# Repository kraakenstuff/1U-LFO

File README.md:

# 1U-LFO
1U Eurorack LFO module

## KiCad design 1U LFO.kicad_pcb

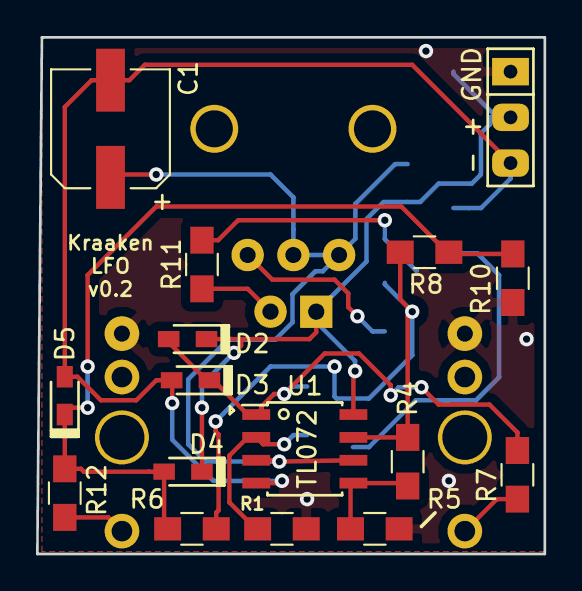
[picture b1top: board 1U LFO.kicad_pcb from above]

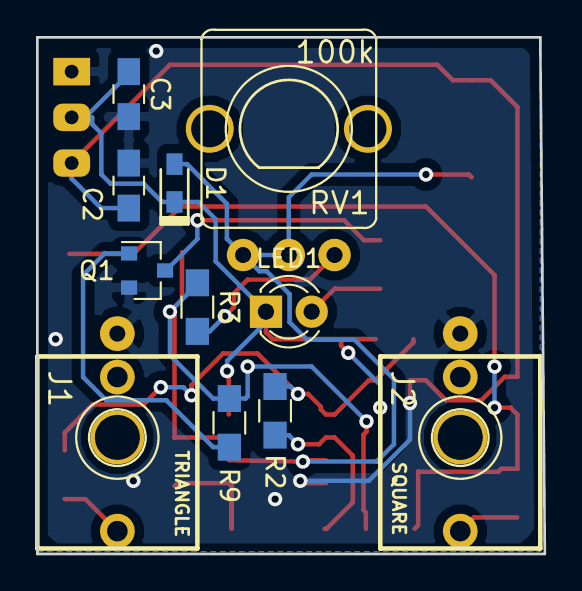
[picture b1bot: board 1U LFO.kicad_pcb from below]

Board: 2 copper layers, 28.2 x 28.7 mm, 27 parts (11 on the bottom side), 15 nets.

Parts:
- + GND: Header_1x03; Header 1x3
C1: 33uF; CP_Elec_6.3x5.3
C2, C3: 100nF; C_0805_HandSoldering
D1, D2, D3, D4, D5: 1N4148; D_0805_HandSoldering
J1: TRIANGLE; PJ301M-12
J2: SQUARE; PJ301M-12
LED1: LED; LED_D3.0mm_FlatTop
Q1: MMBT3904; SOT-23
R1: 5.6k; R_0805_HandSoldering
R2, R5, R6: 15k; R_0805_HandSoldering
R3, R11: 2.2k; R_0805_HandSoldering
R4, R9: 100k; R_0805_HandSoldering
R7, R12: 470R; R_0805_HandSoldering
R8: 220k; R_0805_HandSoldering
R10: 10k; R_0805_HandSoldering
RV1: 100k; POT-9MM-ALPHA
U1: TL072; SOIC-8_3.9x4.9mm_Pitch1.27mm

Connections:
+12V: - + GND.2, C3.1, D1.1, D2.1, D4.1, LED1.1, U1.8
-12V: - + GND.3, C1.2, C2.1, D3.2, D5.2, U1.4
GND: - + GND.1, C2.2, C3.2, J1.1, J2.1, Q1.2, R1.2, R5.2, R10.2
unnamed: C1.1, D1.2, RV1.1, RV1.2, U1.3, U1.6
unnamed: D2.2, D3.1, R2.1, R7.2, U1.1
unnamed: D4.2, D5.1, R6.1, R8.1, R10.1, R12.2
unnamed: J1.3, R7.1
unnamed: J2.3, R12.1
unnamed: LED1.2, R11.1
unnamed: Q1.1, R9.2
unnamed: Q1.3, R11.2
unnamed: R1.1, R2.2, U1.2
unnamed: R3.1, RV1.3
unnamed: R3.2, R4.1, R6.2, R8.2, R9.1, U1.7
unnamed: R4.2, R5.1, U1.5
